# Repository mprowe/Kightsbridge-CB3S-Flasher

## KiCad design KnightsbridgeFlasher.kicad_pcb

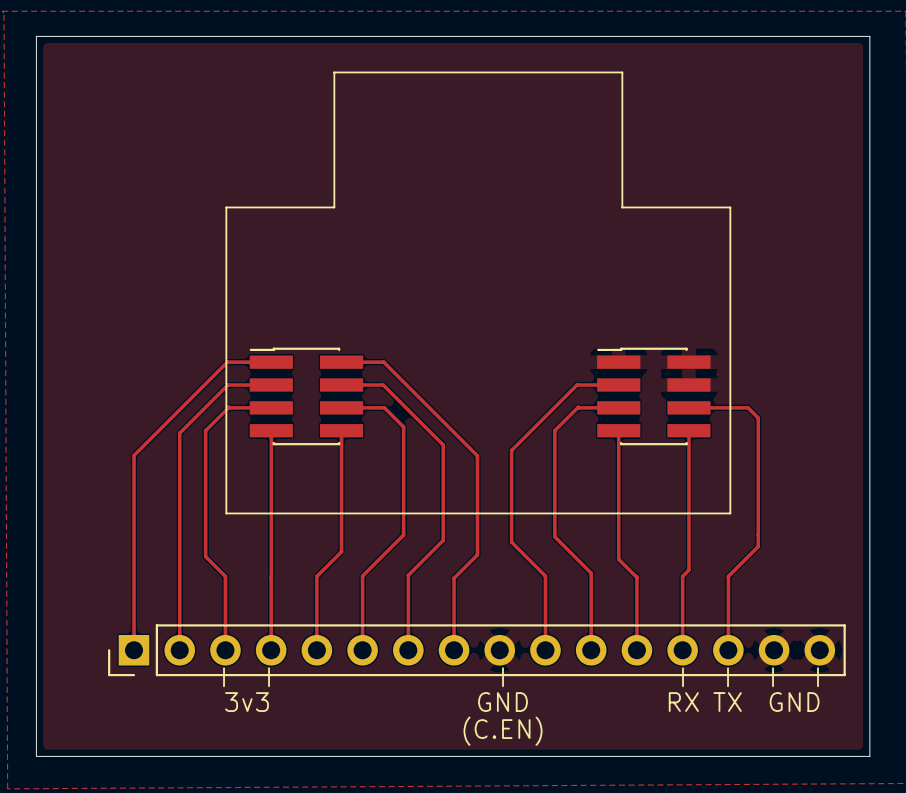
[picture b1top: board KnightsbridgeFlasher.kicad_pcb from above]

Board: 2 copper layers, 46.3 x 40.0 mm, 3 parts (0 on the bottom side), 13 nets.

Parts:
Com3, Com4: Conn_02x04_Odd_Even; PinHeader_2x04_P1.27mm_Vertical_SMD
J1: Conn_01x16; PinHeader_1x16_P2.54mm_Vertical

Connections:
+3V3: Com4.5, Com4.7, J1.3 (3v3), J1.4 (3v3)
GND: Com3.1, Com3.2, Com3.4, J1.9 (GND), J1.15 (GND), J1.16 (GND)
unnamed: Com3.3, J1.10
unnamed: Com3.5, J1.11
unnamed: Com3.6, J1.14 (TX1)
unnamed: Com3.7, J1.12
unnamed: Com3.8, J1.13 (RX1)
unnamed: Com4.1, J1.1
unnamed: Com4.2, J1.8
unnamed: Com4.3, J1.2
unnamed: Com4.4, J1.7
unnamed: Com4.6, J1.6
unnamed: Com4.8, J1.5
